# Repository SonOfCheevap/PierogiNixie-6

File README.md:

# PierogiNixie-6
A Pi Pico powered nixie tube board that uses 6 IN-14 nixie tubes.

## New with V2.1
- Replaced L7805 Regulator with a TI Buck Converter
- Improved routing of power, with larger traces
- Slightly Wider
- Improved Layout

# Features
- Programmed using a Pi Pico
- ds3231m RTC
- CR2032 Battery for keeping time when off power
- 6x IN-14 Nixie Tubes
- 6x k155id1 Binary to Decimal decoders
- Onboard (and now larger) 12v to 5v Convertor (V2)
- MCP23017-E/SO IO expander
- Buttons that can be programmed to adjust the time
- Breakout header for easier connectivity to a pico probe
- Mounting holes for 4 M3.5x6 screws

# Photos
AS OF 12/20/23

Top

Bottom

Front

Back

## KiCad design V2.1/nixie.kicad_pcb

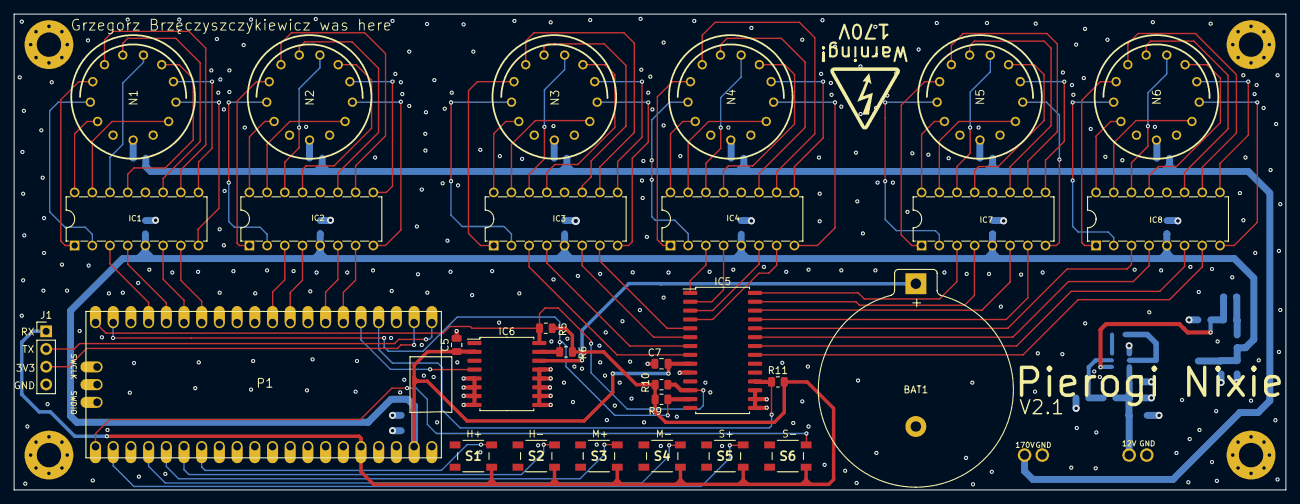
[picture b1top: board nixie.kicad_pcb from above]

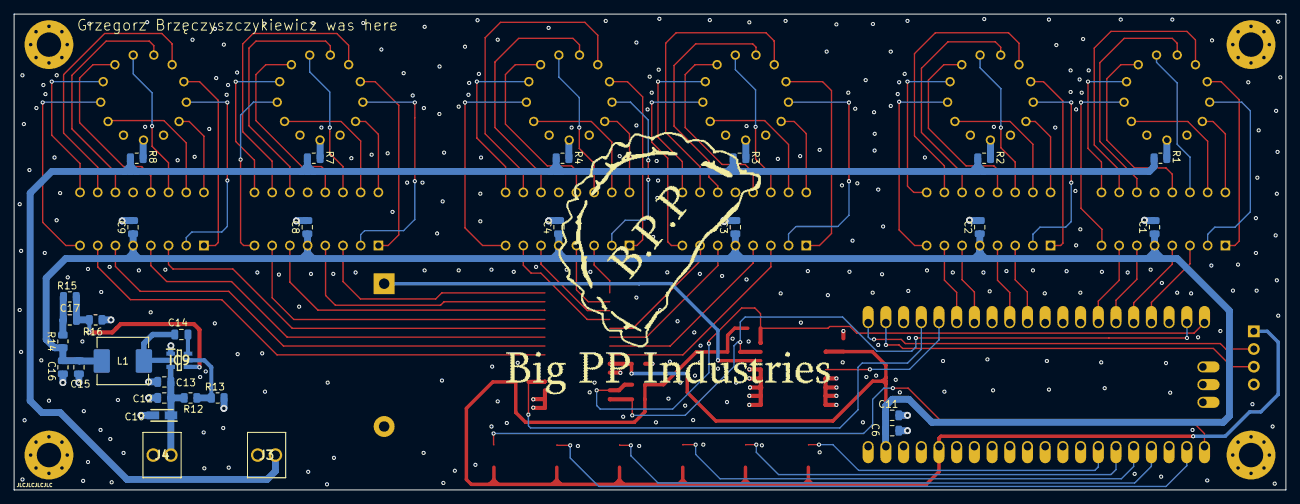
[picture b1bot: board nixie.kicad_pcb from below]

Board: 4 copper layers, 182.5 x 68.3 mm, 66 parts (37 on the bottom side), 113 nets.

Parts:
BAT1: 36-106-ND; BatteryHolder_Keystone_106_1x20mm
C1, C2, C3, C4, C5, C6, C7, C8, C9: 100nf; C_0805_2012Metric
C10: 47uF; CAPPM3216X180N
C11, C12: 10uF; C_0805_2012Metric
C13, C14: .1uF; C_0805_2012Metric
C15, C16: 22uF; C_0805_2012Metric
C17: 75pF; C_0805_2012Metric
H1, H2, H3, H4: MountingHole; MountingHole_3.5mm_Pad_Via
IC1, IC2, IC3, IC4, IC7, IC8: K155ID1; DIP16-2.54-19.2X7.62MM
IC5: MCP23017-E_SO; SOIC-28W_7.5x17.9mm_P1.27mm
IC6: DS3231M+TRL; SOIC-16W_7.5x10.3mm_P1.27mm
IC9: TPS54302DDCT; SOT95P280X110-6N
J1: M20-9990446; PinHeader_1x04_P2.54mm_Vertical
J3, J4: OSTVN02A150
L1: 10uH; L_Abracon_ASPI-0630LR
N1, N2, N3, N4, N5, N6: IN-14
P1: RPI_PICO-TH; RPI_PICO_TH
R1, R2, R3, R4, R5, R6, R7, R8, R9, R10, R11: 10k; R_0805_2012Metric
R12: 511K; R_0805_2012Metric
R13: 105K; R_0805_2012Metric
R14: 49.9; R_0805_2012Metric
R15: 100K; R_0805_2012Metric
R16: 13.3K; R_0805_2012Metric
S1, S2, S3, S4, S5, S6: PTS647SN50SMTR2LFS
U$2: HVSMALL
U$3: BIGPP

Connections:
+3V3: J1.1, P1.3V3, R5.1, R6.2, R9.1, R10.1, R11.2, S1.4, S2.4, S3.4, S4.4, S5.4, S6.4
+5V: C1.1, C2.1, C3.1, C4.1, C5.1, C6.1, C7.1, C8.1, C9.1, C11.1, C15.1, C16.1, IC1.5 (VCC), IC2.5 (VCC), IC3.5 (VCC), IC4.5 (VCC), IC5.9 (VDD), IC6.2 (VCC), IC7.5 (VCC), IC8.5 (VCC), L1.2, P1.VSYS, R14.1
+12V: C10.1, C12.1, C13.1, IC9.3 (VIN), J4.1, R12.1
/170V1: N1.A, R1.2
/170V2: N2.A, R2.2
/170V3: N3.A, R3.2
/170V4: N4.A, R4.2
/170V5: N5.A, R7.1
/170V6: N6.A, R8.1
/A1: IC1.3 (A), P1.GP13
/A2: IC2.3 (A), P1.GP7
/A3: IC3.3 (A), IC5.8 (GPB7)
/A4: IC4.3 (A), IC5.1 (GPB0)
/A5: IC5.28 (GPA7), IC7.3 (A)
/A6: IC5.24 (GPA3), IC8.3 (A)
/B1: IC1.6 (B), P1.GP11
/B2: IC2.6 (B), P1.GP5
/B3: IC3.6 (B), IC5.6 (GPB5)
/B4: IC4.6 (B), IC5.3 (GPB2)
/B5: IC5.26 (GPA5), IC7.6 (B)
/B6: IC5.22 (GPA1), IC8.6 (B)
/C1: IC1.7 (C), P1.GP10
/C2: IC2.7 (C), P1.GP4
/C3: IC3.7 (C), IC5.5 (GPB4)
/C4: IC4.7 (C), IC5.4 (GPB3)
/C5: IC5.25 (GPA4), IC7.7 (C)
/C6: IC5.21 (GPA0), IC8.7 (C)
/D1: IC1.4 (D), P1.GP12
/D2: IC2.4 (D), P1.GP6
/D3: IC3.4 (D), IC5.7 (GPB6)
/D4: IC4.4 (D), IC5.2 (GPB1)
/D5: IC5.27 (GPA6), IC7.4 (D)
/D6: IC5.23 (GPA2), IC8.4 (D)
/N10: IC1.16 (0), N1.0
/N11: IC1.15 (1), N1.1
/N12: IC1.8 (2), N1.2
/N13: IC1.9 (3), N1.3
/N14: IC1.13 (4), N1.4
/N15: IC1.14 (5), N1.5
/N16: IC1.11 (6), N1.6
/N17: IC1.10 (7), N1.7
/N18: IC1.1 (8), N1.8
/N19: IC1.2 (9), N1.9
/N20: IC2.16 (0), N2.0
/N21: IC2.15 (1), N2.1
/N22: IC2.8 (2), N2.2
/N23: IC2.9 (3), N2.3
/N24: IC2.13 (4), N2.4
/N25: IC2.14 (5), N2.5
/N26: IC2.11 (6), N2.6
/N27: IC2.10 (7), N2.7
/N28: IC2.1 (8), N2.8
/N29: IC2.2 (9), N2.9
/N30: IC3.16 (0), N3.0
/N31: IC3.15 (1), N3.1
/N32: IC3.8 (2), N3.2
/N33: IC3.9 (3), N3.3
/N34: IC3.13 (4), N3.4
/N35: IC3.14 (5), N3.5
/N36: IC3.11 (6), N3.6
/N37: IC3.10 (7), N3.7
/N38: IC3.1 (8), N3.8
/N39: IC3.2 (9), N3.9
/N40: IC4.16 (0), N4.0
/N41: IC4.15 (1), N4.1
/N42: IC4.8 (2), N4.2
/N43: IC4.9 (3), N4.3
/N44: IC4.13 (4), N4.4
/N45: IC4.14 (5), N4.5
/N46: IC4.11 (6), N4.6
/N47: IC4.10 (7), N4.7
/N48: IC4.1 (8), N4.8
/N49: IC4.2 (9), N4.9
/N50: IC7.16 (0), N5.0
/N51: IC7.15 (1), N5.1
/N52: IC7.8 (2), N5.2
/N53: IC7.9 (3), N5.3
/N54: IC7.13 (4), N5.4
/N55: IC7.14 (5), N5.5
/N56: IC7.11 (6), N5.6
/N57: IC7.10 (7), N5.7
/N58: IC7.1 (8), N5.8
/N59: IC7.2 (9), N5.9
/N60: IC8.16 (0), N6.0
/N61: IC8.15 (1), N6.1
/N62: IC8.8 (2), N6.2
/N63: IC8.9 (3), N6.3
/N64: IC8.13 (4), N6.4
/N65: IC8.14 (5), N6.5
/N66: IC8.11 (6), N6.6
/N67: IC8.10 (7), N6.7
/N68: IC8.1 (8), N6.8
/N69: IC8.2 (9), N6.9
/RSTC: IC6.4 (~RST), P1.GP3
/RSTIO: IC5.18 (~RESET), P1.GP2, R11.1
/RX: J1.2, P1.GP0
/S1: P1.GP21, S1.1
/S2: P1.GP20, S2.1
/S3: P1.GP19, S3.1
/S4: P1.GP18, S4.1
/S5: P1.GP17, S5.1
/S6: P1.GP16, S6.1
/SCL1: IC5.12 (SCK), IC6.16 (SCL), P1.GP15, R5.2, R10.2
/SDA1: IC5.13 (SDA), IC6.15 (SDA), P1.GP14, R6.1, R9.2
/TX: J1.3, P1.GP1
GND: BAT1.2 (-), C1.2, C2.2, C3.2, C4.2, C5.2, C6.2, C7.2, C8.2, C9.2, C10.2, C11.2, C12.2, C13.2, C15.2, C16.2, IC1.12 (GND), IC2.12 (GND), IC3.12 (GND), IC4.12 (GND), IC5.10 (VSS), IC5.15 (A0), IC5.16 (A1), IC5.17 (A2), IC6.5 (GND), IC6.6 (GND), IC6.7 (GND), IC6.8 (GND), IC6.9 (GND), IC6.10 (GND), IC6.11 (GND), IC6.12 (GND), IC6.13 (GND), IC7.12 (GND), IC8.12 (GND), IC9.1 (GND), J1.4, J3.2, J4.2, P1.AGND, P1.GND@1 (GND), P1.GND@2 (GND), P1.GND@3 (GND), P1.GND@4 (GND), P1.GND@5 (GND), P1.GND@6 (GND), P1.GND@7 (GND), P1.GND@8 (GND), R13.2, R16.2
unnamed: BAT1.1 (+), IC6.14 (VBAT)
unnamed: C17.1, R14.2, R15.1
unnamed: C14.1, IC9.6 (BOOT)
unnamed: IC9.5 (EN), R12.2, R13.1
unnamed: C17.2, IC9.4 (FB), R15.2, R16.1
unnamed: C14.2, IC9.2 (SW), L1.1
VCC: J3.1, R1.1, R2.1, R3.1, R4.1, R7.2, R8.2

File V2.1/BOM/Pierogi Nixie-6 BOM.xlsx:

Part ID | Part Description | Item Link | Cost Per | # Needed | Total
P1 | PI Pico | https://www.digikey.com/en/products/detail/raspberry-pi/SC09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 | 4.0 | 1.0 | 4
J1 | M20-9990446 | https://www.digikey.com/en/products/detail/harwin-inc/M20-99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 | 0.21 | 1.0 | 0.21
J3, J4 | OSTVN02A150 | https://www.digikey.com/en/products/detail/on-shore-technolo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 | 0.92 | 2.0 | 1.84
IC1, IC2, IC3, IC4, IC7, IC8 | K155ID1 | https://www.ebay.com/itm/183563404353?hash=item2abd3b4441:g: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 | 2.98 | 6.0 | 17.88
IC5 | MCP23017-E_SO | https://www.digikey.com/en/products/detail/microchip-technol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 | 1.62 | 1.0 | 1.62
IC6 | DS3231M+TRL | https://www.digikey.com/en/products/detail/analog-devices-in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 | 9.81 | 1.0 | 9.81
IC9 | TPS54302DDCT | https://www.digikey.com/en/products/detail/texas-instruments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 | 2.01 | 1.0 | 2.01
N1, N2, N3, N4, N5, N6 | IN-14 Nixie Tubes | N/A | 10.0 | 6.0 | 60
BAT1 | CR2032 Battery Holder | https://www.digikey.com/en/products/detail/keystone-electron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 | 1.34 | 1.0 | 1.34
S1, S2, S3, S4, S5, S6 | PTS647SN50SMTR2LFS | https://www.digikey.com/en/products/detail/c-k/pts-647-sn50-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 | 0.2 | 6.0 | 1.2
C1, C2, C3, C4, C5, C6, C7, C8, C9, C11, C13, C14 | 0805 100nf/.1uF Capacitor | https://www.digikey.com/en/products/detail/samsung-electro-m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 | 0.1 | 11.0 | 1.1
C10 | 47uF | https://www.digikey.com/en/products/detail/kyocera-avx/F931A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 | 0.72 | 10.0 | 7.2
C11, C12 | 10uF | https://www.digikey.com/en/products/detail/samsung-electro-m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 | 0.1 | 2.0 | 0.2
C15, C16 | 22uF | https://www.digikey.com/en/products/detail/samsung-electro-m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 | 0.33 | 2.0 | 0.66
C17 | 75pF | https://www.digikey.com/en/products/detail/yageo/CC0805JRNPO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 | 0.14 | 1.0 | 0.14
R1, R2, R3, R4, R5, R6, R7, R8, R9, R10, R11 | 0805 10K Resistor | https://www.digikey.com/en/products/detail/vishay-dale/RCS08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 | 0.1 | 11.0 | 1.1
R12 | 511K | https://www.digikey.com/en/products/detail/koa-speer-electro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 | 0.19 | 1.0 | 0.19
R13 | 105K | https://www.digikey.com/en/products/detail/koa-speer-electro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 | 0.1 | 1.0 | 0.1
R14 | 49.9 ohm | https://www.digikey.com/en/products/detail/vishay-dale/CRCW0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 | 0.2 | 1.0 | 0.2
R15 | 100K | https://www.digikey.com/en/products/detail/koa-speer-electro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 | 0.18 | 1.0 | 0.18
R16 | 13.3K | https://www.digikey.com/en/products/detail/vishay-dale/CRCW0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 | 0.2 | 1.0 | 0.2
L1 | 10uH | https://www.digikey.com/en/products/detail/abracon-llc/ASPI-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 | 0.72 | 1.0 | 0.72
Misc | K155ID1 Chip Sockets | https://www.digikey.com/en/products/detail/on-shore-technolo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 | 0.26 | 6.0 | 1.56
Misc | 20 pin male header | https://www.digikey.com/en/products/detail/adam-tech/PH1-20-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 | 0.32 | 6.0 | 1.92
Misc | 20 pin female header | https://www.digikey.com/en/products/detail/sullins-connector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 | 1.23 | 1.0 | 1.23
Misc | 3 pin male header | https://www.digikey.com/en/products/detail/sullins-connector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 | 0.37 | 1.0 | 0.37
Misc | 3 female header | https://www.digikey.com/en/products/detail/sullins-connector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 | 0.09 | 1.0 | 0.09
Board | PierogiNixie-6 | N/A | 7.0 | 1.0 | 7
 |  |  |  | Final Total: | 124.07

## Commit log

2023-07-02 WIP files
2023-07-02 Changes to schematic
2023-07-04 Started routing
2023-07-06 made minor changes to routing
2023-07-07 added vias, made small routing adjustments
2023-07-08 added reset line for clock
2023-12-14 Started v1.1, schematic redone, board WIP'
2023-12-14 Reorganizing Repo
2023-12-15 Adjsuted more items in schematic, began layout
2023-12-20 Continued routing
2023-12-21 Finished routing, added vias
2023-12-21 Added a few extra vias
2023-12-21 Updated images, added gerbers
2023-12-28 Updated bom, slightchanges to footprint indicators
